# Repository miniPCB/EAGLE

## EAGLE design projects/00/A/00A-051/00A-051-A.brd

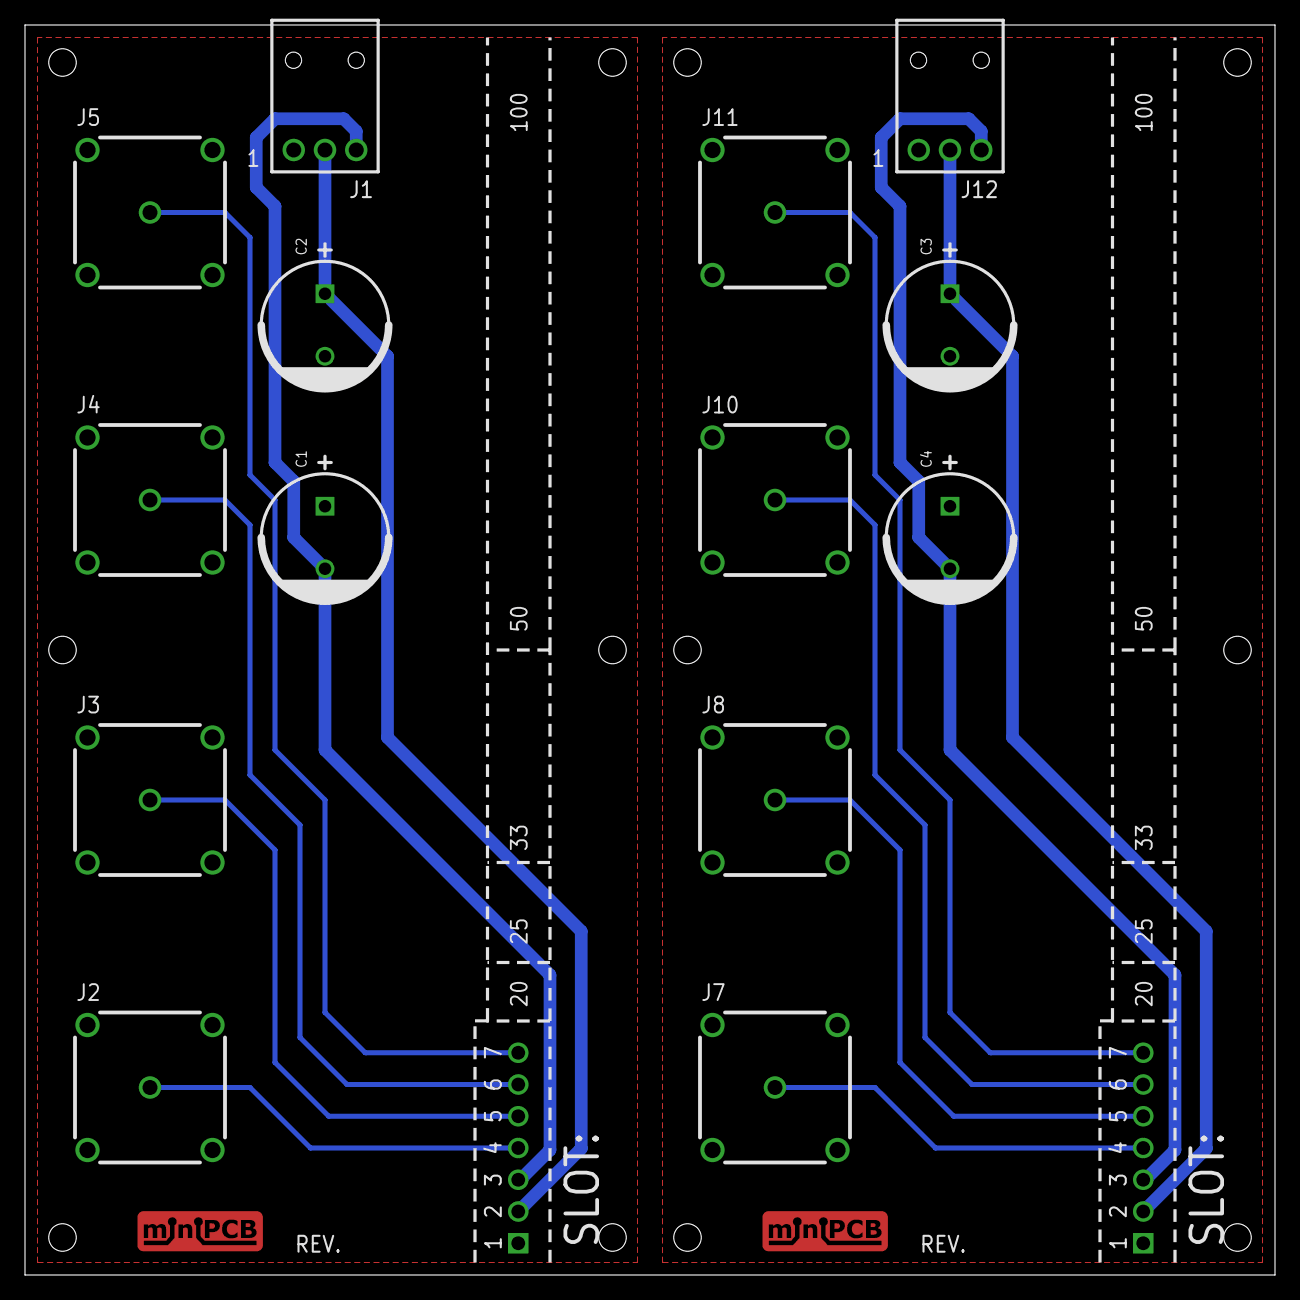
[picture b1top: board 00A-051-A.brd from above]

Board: 2 copper layers, 100.0 x 100.0 mm, 18 parts (0 on the bottom side), 14 nets.

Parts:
C1, C2, C3, C4: C5MM
J1, J12: NANOFIT-105313-1103; PINS_3-NANOFIT-H
J2, J7: J5.4; B35N14H
J3, J4, J5, J8, J10, J11: J5.5; B35N14H
J6, J9: A; MINIPCB_DOCK_7P
PCB, PCB1: MINIPCB_DOCK_50X100

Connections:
CH1: J2.1.SIG, J6.4
CH2: J3.1.SIG, J6.5
CH3: J4.1.SIG, J6.6
CH4: J5.1.SIG, J6.7
CH5: J7.1.SIG, J9.4
CH6: J8.1.SIG, J9.5
CH7: J9.6, J10.1.SIG
CH8: J9.7, J11.1.SIG
GND: C1.+, C2.-, J1.1, J2.2.GND, J2.3.GND, J2.4.GND, J2.5.GND, J3.2.GND, J3.3.GND, J3.4.GND, J3.5.GND, J4.2.GND, J4.3.GND, J4.4.GND, J4.5.GND, J5.2.GND, J5.3.GND, J5.4.GND, J5.5.GND, J6.1
GND1: C3.-, C4.+, J7.2.GND, J7.3.GND, J7.4.GND, J7.5.GND, J8.2.GND, J8.3.GND, J8.4.GND, J8.5.GND, J9.1, J10.2.GND, J10.3.GND, J10.4.GND, J10.5.GND, J11.2.GND, J11.3.GND, J11.4.GND, J11.5.GND, J12.1
V+: C2.+, J1.2, J6.2
V+1: C3.+, J9.2, J12.2
V-: C1.-, J1.3, J6.3
V-1: C4.-, J9.3, J12.3

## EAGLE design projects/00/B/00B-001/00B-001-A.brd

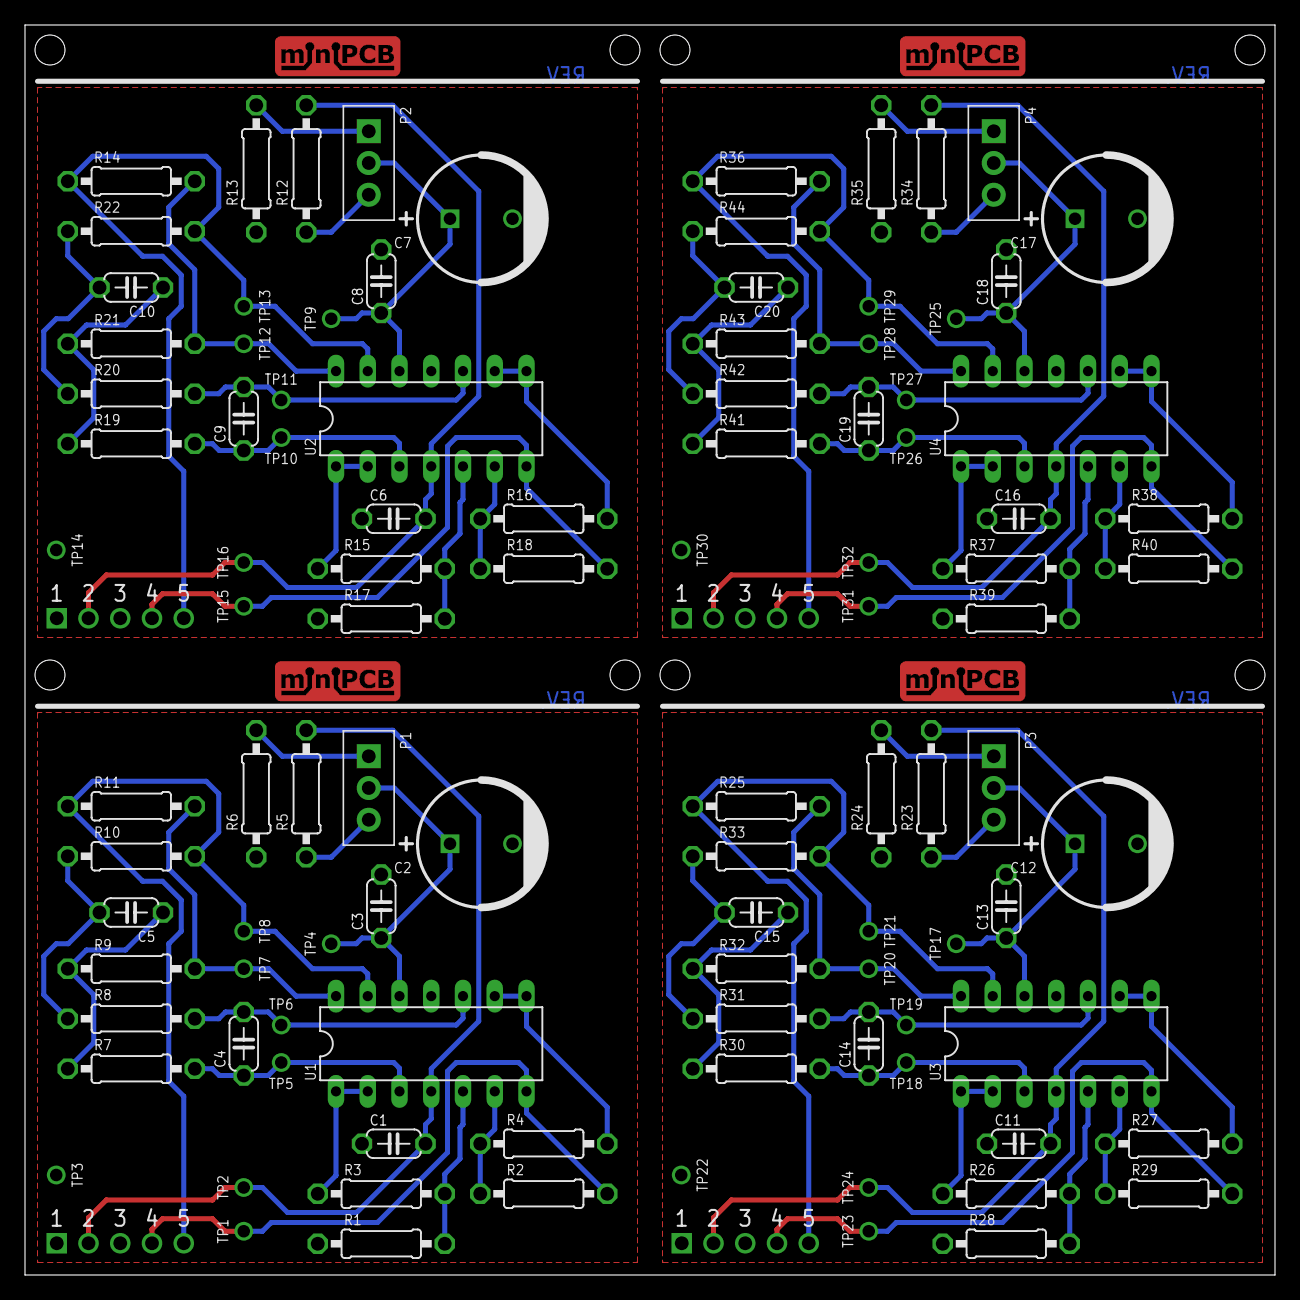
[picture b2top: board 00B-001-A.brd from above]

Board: 2 copper layers, 100.0 x 100.0 mm, 108 parts (0 on the bottom side), 64 nets.

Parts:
C1, C6, C11, C16: 1u; C050-024X044
C2, C7, C12, C17: C5MM
C3, C4, C5, C8, C9, C10, C13, C14, C15, C18, C19, C20: C050-024X044
J7-, J7-1, J7-2, J7-3: MINIPCB_5P_50X50MM
P1, P2, P3, P4: TRIM_0100
R1, R2, R3, R4, R5, R6, R7, R8, R9, R10, R11, R12, R13, R14, R15, R16, R17, R18, R19, R20, R21, R22, R23, R24, R25, R26, R27, R28, R29, R30, R31, R32, R33, R34, R35, R36, R37, R38, R39, R40, R41, R42, R43, R44: 0207/10
TP1, TP2, TP3, TP4, TP5, TP6, TP7, TP8, TP9, TP10, TP11, TP12, TP13, TP14, TP15, TP16, TP17, TP18, TP19, TP20, TP21, TP22, TP23, TP24, TP25, TP26, TP27, TP28, TP29, TP30, TP31, TP32: PINS_1_TESTPOINT_KE5000_NOTEXT
U1, U2, U3, U4: 324; DIL14

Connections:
GND: C1.2, C2.-, C3.2, J7-.1, R1.2, R6.1, TP3.1, U1.11
GND1: C6.2, C7.-, C8.2, J7-1.1, R13.1, R17.2, TP14.1, U2.11
GND2: C11.2, C12.-, C13.2, J7-2.1, R24.1, R28.2, TP22.1, U3.11
GND3: C16.2, C17.-, C18.2, J7-3.1, R35.1, R39.2, TP30.1, U4.11
unnamed: R9.1, R11.1, TP7.1, U1.14
unnamed: R3.1, U1.1, U1.2
unnamed: R4.1, U1.8, U1.9
unnamed: C2.+, C3.1, P1.2, TP4.1, U1.12
unnamed: P1.1, R6.2
unnamed: P1.3, R5.1
unnamed: J7-.5, R10.1, R11.2, TP8.1, U1.13
unnamed: R2.1, R4.2, U1.6
unnamed: R1.1, R3.2, U1.5
unnamed: J7-.4, R2.2, TP1.1, U1.7
unnamed: R14.1, R21.1, TP12.1, U2.14
unnamed: C7.+, C8.1, P2.2, TP9.1, U2.12
unnamed: P2.1, R13.2
unnamed: C4.1, R7.2, TP5.1, U1.3
unnamed: C4.2, R8.2, TP6.1, U1.10
unnamed: C5.1, R7.1, R9.2
unnamed: C5.2, R8.1, R10.2
unnamed: P2.3, R12.1
unnamed: J7-1.5, R14.2, R22.1, TP13.1, U2.13
unnamed: R15.1, U2.1, U2.2
unnamed: R16.1, U2.8, U2.9
unnamed: R16.2, R18.1, U2.6
unnamed: R15.2, R17.1, U2.5
unnamed: J7-1.4, R18.2, TP15.1, U2.7
unnamed: C9.1, R19.2, TP10.1, U2.3
unnamed: C9.2, R20.2, TP11.1, U2.10
unnamed: C10.1, R19.1, R21.2
unnamed: C10.2, R20.1, R22.2
unnamed: R25.1, R32.1, TP20.1, U3.14
unnamed: C12.+, C13.1, P3.2, TP17.1, U3.12
unnamed: P3.1, R24.2
unnamed: P3.3, R23.1
unnamed: J7-2.5, R25.2, R33.1, TP21.1, U3.13
unnamed: R26.1, U3.1, U3.2
unnamed: R27.1, U3.8, U3.9
unnamed: R27.2, R29.1, U3.6
unnamed: R26.2, R28.1, U3.5
unnamed: J7-2.4, R29.2, TP23.1, U3.7
unnamed: C14.1, R30.2, TP18.1, U3.3
unnamed: C14.2, R31.2, TP19.1, U3.10
unnamed: C15.1, R30.1, R32.2
unnamed: C15.2, R31.1, R33.2
unnamed: R36.1, R43.1, TP28.1, U4.14
unnamed: C17.+, C18.1, P4.2, TP25.1, U4.12
unnamed: P4.1, R35.2
unnamed: P4.3, R34.1
unnamed: J7-3.5, R36.2, R44.1, TP29.1, U4.13
unnamed: R37.1, U4.1, U4.2
unnamed: R38.1, U4.8, U4.9
unnamed: R38.2, R40.1, U4.6
unnamed: R37.2, R39.1, U4.5
unnamed: J7-3.4, R40.2, TP31.1, U4.7
unnamed: C19.1, R41.2, TP26.1, U4.3
unnamed: C19.2, R42.2, TP27.1, U4.10
unnamed: C20.1, R41.1, R43.2
unnamed: C20.2, R42.1, R44.2
V+: C1.1, J7-.2, R5.2, TP2.1, U1.4
V+1: C6.1, J7-1.2, R12.2, TP16.1, U2.4
V+2: C11.1, J7-2.2, R23.2, TP24.1, U3.4
V+3: C16.1, J7-3.2, R34.2, TP32.1, U4.4

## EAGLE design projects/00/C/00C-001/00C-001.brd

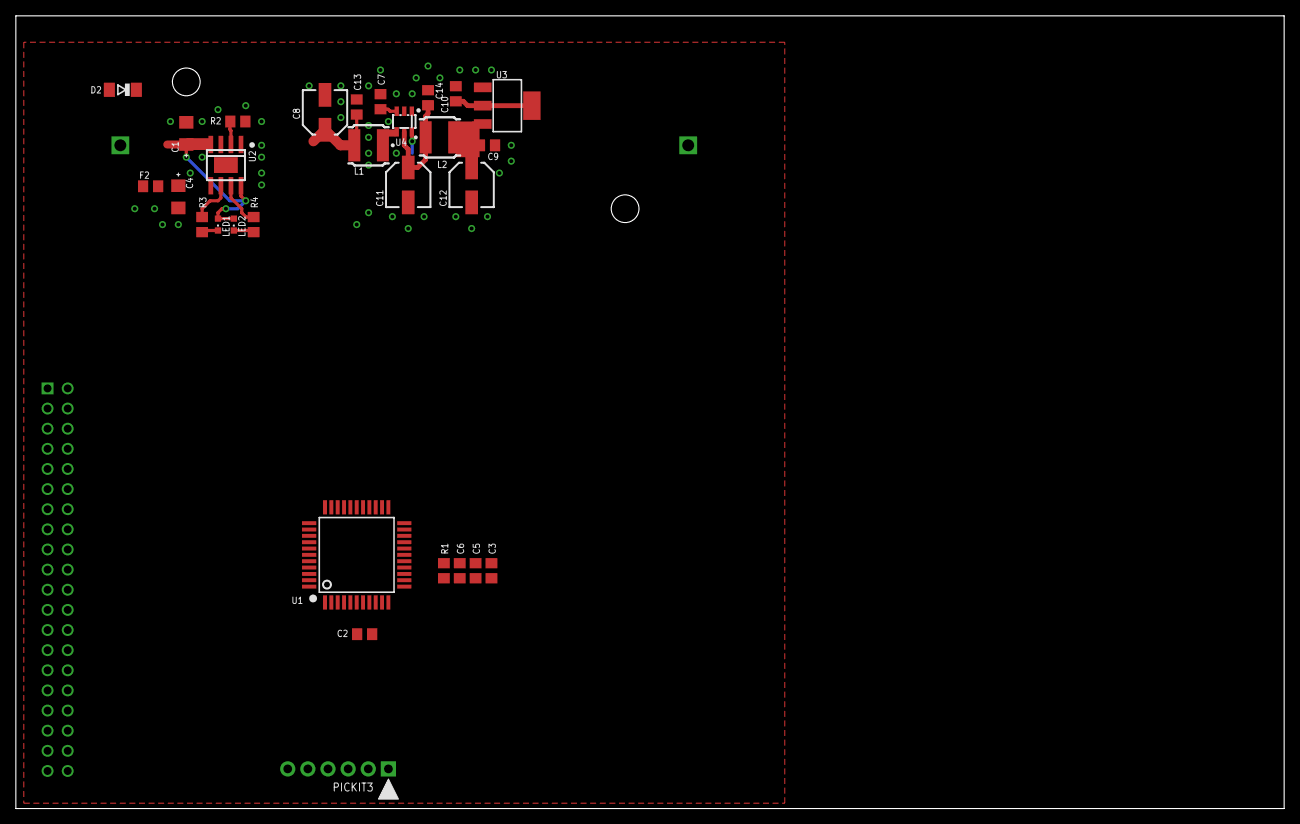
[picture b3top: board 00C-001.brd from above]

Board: 2 copper layers, 160.0 x 100.0 mm, 31 parts (1 on the bottom side), 20 nets.

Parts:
B1: 1043; BATTERY-18650-1
C1, C4: 10u, 1206; C1206
C2, C3, C5, C6: C0805
C7, C9, C10, C13, C14: 1u; C0805
C8, C11, C12: 47u; C-WE-5MM
D2: 1N5819; SOD80C
F2: 0805; F0805
J1-: RPI ZERO; RPI_ZERO
L1, L2: 22u; SRN5040
LED1: SBY; CHIPLED_0603
LED2: CHG; CHIPLED_0603
R1: R0805
R2: RPROG; R0805
R3, R4: 1k; R0805
U1: SQFP-S-10X10-44
U2: TP4056; SO08-THERMAL
U3: AMS1117-3.3; SOT223
U4: AP1603; SOT23-6
U$401: PICKIT3; PINS_6_PICKIT3

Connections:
+3V3: C10.2, U3.2, U3.4.TAB
+5V: C9.2, C12.1+, L2.1, U3.3
+BAT: C4.+, C8.1+, C13.2, F2.2, L1.1, U2.5
B+: B1.+, F2.1
CHARGE: R4.2, U2.7
DCDC_OUT: C11.1+, C14.2, L2.2, U4.5
DCDC_REF: C7.2, U4.3
GND: B1.1, C1.-, C2.2, C3.2, C4.-, C5.2, C6.2, C7.1, C8.2-, C9.1, C10.1, C11.2-, C12.2-, C13.1, C14.1, J1-.6, J1-.9, J1-.14, J1-.20, J1-.25, J1-.30, J1-.34, J1-.39, R2.1, U1.6, U1.29, U2.1, U2.3, U2.THERMAL, U3.1, U4.1, U4.2, U$401.3
unnamed: LED1.C, R3.1
unnamed: LED2.C, R4.1
unnamed: R2.2, U2.2
unnamed: U1.17, U$401.4
unnamed: U1.16, U$401.5
unnamed: R1.2, U1.18, U$401.1
PIC.RX: J1-.8, U1.1
PIC.TX: J1-.10, U1.44
PIC_VDD: C2.1, C3.1, C5.1, C6.1, R1.1, U1.7, U1.28, U$401.2
STANDBY: R3.2, U2.6
SWITCH_NODE: L1.2, U4.4
VCC: C1.+, D2.C, LED1.A, LED2.A, U2.4, U2.8

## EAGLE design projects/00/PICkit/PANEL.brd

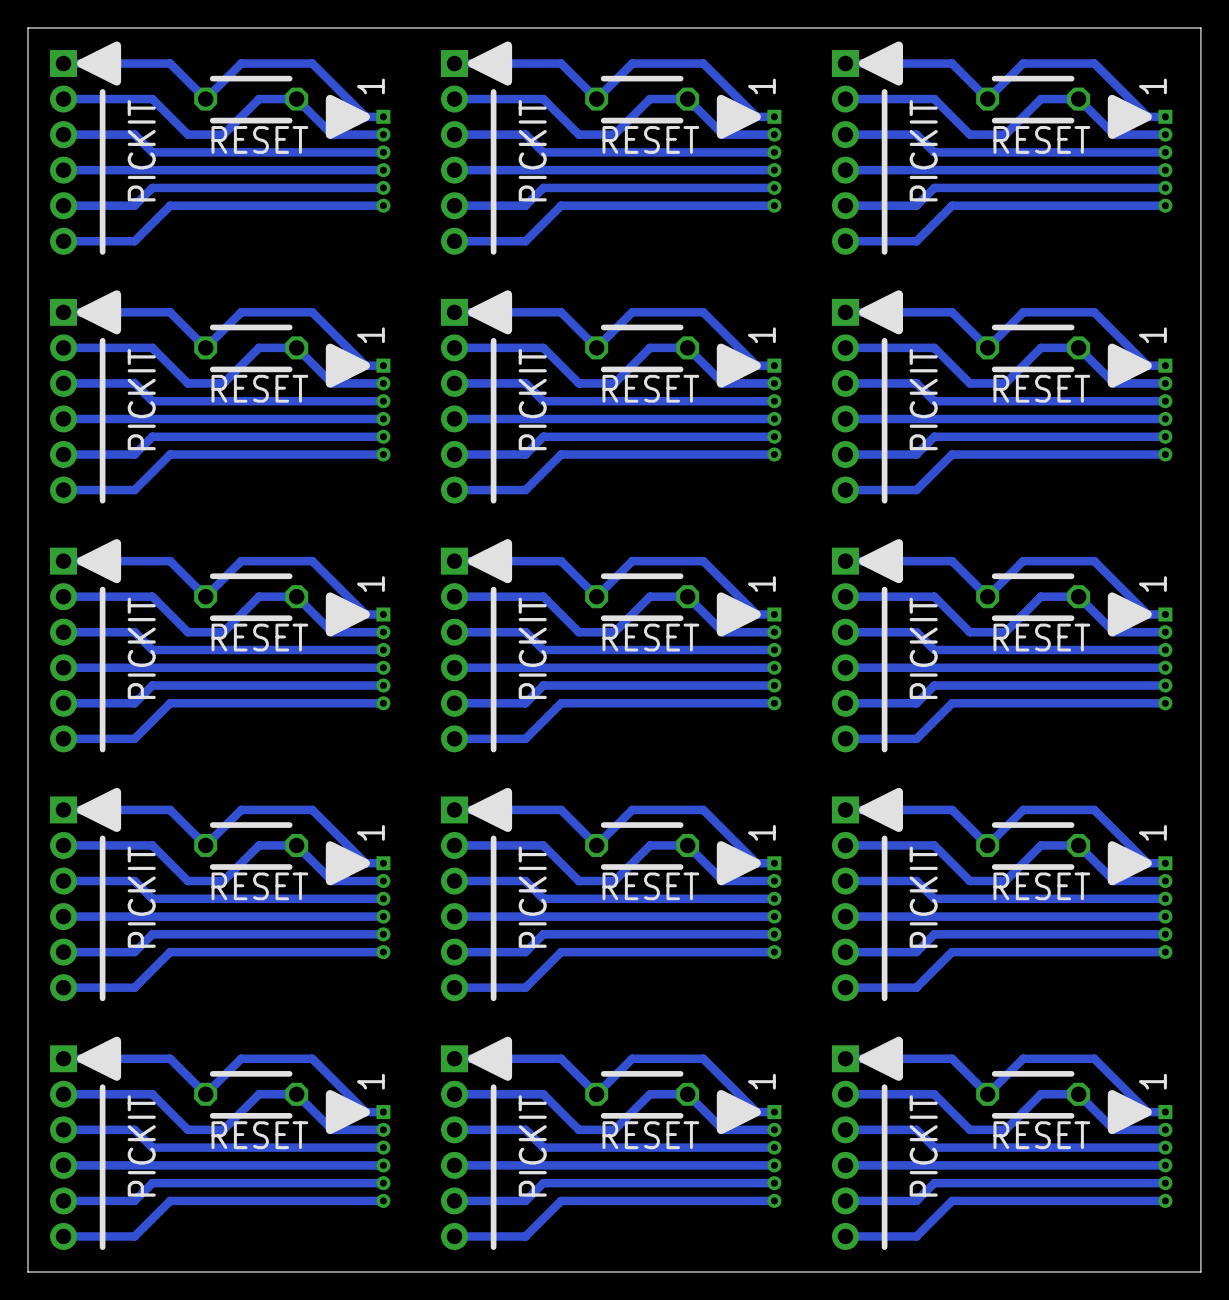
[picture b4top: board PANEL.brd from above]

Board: 2 copper layers, 83.8 x 88.9 mm, 45 parts (0 on the bottom side), 90 nets.

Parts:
RESET, RESET1, RESET2, RESET3, RESET4, RESET5, RESET6, RESET7, RESET8, RESET9, RESET10, RESET11, RESET12, RESET13, RESET14: 3X6MM
U$1, U$2, U$5, U$7, U$9, U$11, U$13, U$15, U$17, U$19, U$21, U$23, U$25, U$27, U$29: PICKIT3/1.27; PINS_6_1MM27
U$3, U$4, U$6, U$8, U$10, U$12, U$14, U$16, U$18, U$20, U$22, U$24, U$26, U$28, U$30: PICKIT; PINS_6_PICKIT3_TEXT

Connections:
unnamed: RESET.1, U$2.1, U$3.1
unnamed: RESET.2, U$2.2, U$3.2
unnamed: U$2.3, U$3.3
unnamed: U$2.4, U$3.4
unnamed: U$2.5, U$3.5
unnamed: U$2.6, U$3.6
unnamed: RESET1.1, U$1.1, U$4.1
unnamed: RESET1.2, U$1.2, U$4.2
unnamed: U$1.3, U$4.3
unnamed: U$1.4, U$4.4
unnamed: U$1.5, U$4.5
unnamed: U$1.6, U$4.6
unnamed: RESET2.1, U$5.1, U$6.1
unnamed: RESET2.2, U$5.2, U$6.2
unnamed: U$5.3, U$6.3
unnamed: U$5.4, U$6.4
unnamed: U$5.5, U$6.5
unnamed: U$5.6, U$6.6
unnamed: RESET3.1, U$7.1, U$8.1
unnamed: RESET3.2, U$7.2, U$8.2
unnamed: U$7.3, U$8.3
unnamed: U$7.4, U$8.4
unnamed: U$7.5, U$8.5
unnamed: U$7.6, U$8.6
unnamed: RESET4.1, U$9.1, U$10.1
unnamed: RESET4.2, U$9.2, U$10.2
unnamed: U$9.3, U$10.3
unnamed: U$9.4, U$10.4
unnamed: U$9.5, U$10.5
unnamed: U$9.6, U$10.6
unnamed: RESET5.1, U$11.1, U$12.1
unnamed: RESET5.2, U$11.2, U$12.2
unnamed: U$11.3, U$12.3
unnamed: U$11.4, U$12.4
unnamed: U$11.5, U$12.5
unnamed: U$11.6, U$12.6
unnamed: RESET6.1, U$13.1, U$14.1
unnamed: RESET6.2, U$13.2, U$14.2
unnamed: U$13.3, U$14.3
unnamed: U$13.4, U$14.4
unnamed: U$13.5, U$14.5
unnamed: U$13.6, U$14.6
unnamed: RESET7.1, U$15.1, U$16.1
unnamed: RESET7.2, U$15.2, U$16.2
unnamed: U$15.3, U$16.3
unnamed: U$15.4, U$16.4
unnamed: U$15.5, U$16.5
unnamed: U$15.6, U$16.6
unnamed: RESET8.1, U$17.1, U$18.1
unnamed: RESET8.2, U$17.2, U$18.2
unnamed: U$17.3, U$18.3
unnamed: U$17.4, U$18.4
unnamed: U$17.5, U$18.5
unnamed: U$17.6, U$18.6
unnamed: RESET9.1, U$19.1, U$20.1
unnamed: RESET9.2, U$19.2, U$20.2
unnamed: U$19.3, U$20.3
unnamed: U$19.4, U$20.4
unnamed: U$19.5, U$20.5
unnamed: U$19.6, U$20.6
unnamed: RESET10.1, U$21.1, U$22.1
unnamed: RESET10.2, U$21.2, U$22.2
unnamed: U$21.3, U$22.3
unnamed: U$21.4, U$22.4
unnamed: U$21.5, U$22.5
unnamed: U$21.6, U$22.6
unnamed: RESET11.1, U$23.1, U$24.1
unnamed: RESET11.2, U$23.2, U$24.2
unnamed: U$23.3, U$24.3
unnamed: U$23.4, U$24.4
unnamed: U$23.5, U$24.5
unnamed: U$23.6, U$24.6
unnamed: RESET12.1, U$25.1, U$26.1
unnamed: RESET12.2, U$25.2, U$26.2
unnamed: U$25.3, U$26.3
unnamed: U$25.4, U$26.4
unnamed: U$25.5, U$26.5
unnamed: U$25.6, U$26.6
unnamed: RESET13.1, U$27.1, U$28.1
unnamed: RESET13.2, U$27.2, U$28.2
unnamed: U$27.3, U$28.3
unnamed: U$27.4, U$28.4
unnamed: U$27.5, U$28.5
unnamed: U$27.6, U$28.6
unnamed: RESET14.1, U$29.1, U$30.1
unnamed: RESET14.2, U$29.2, U$30.2
unnamed: U$29.3, U$30.3
unnamed: U$29.4, U$30.4
unnamed: U$29.5, U$30.5
unnamed: U$29.6, U$30.6

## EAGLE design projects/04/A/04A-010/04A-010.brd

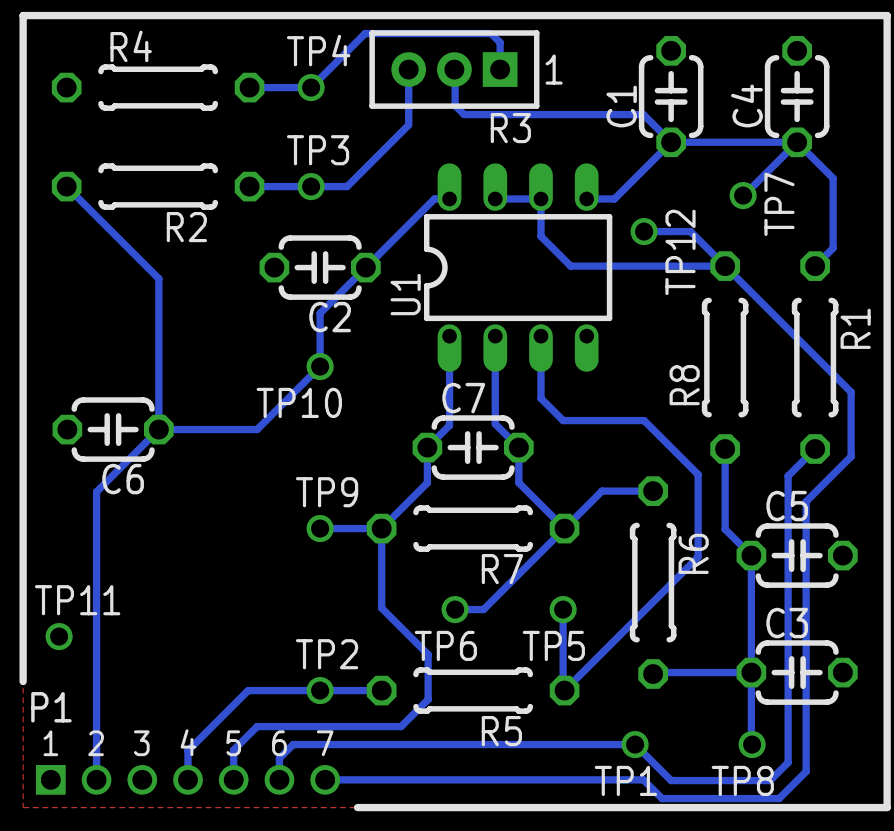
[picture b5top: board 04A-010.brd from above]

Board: 2 copper layers, 29 parts (0 on the bottom side), 12 nets.

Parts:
C1, C2, C3, C4, C5, C6, C7: C050-024X044
P1-: MINIPCB_7P_50X50
R1, R2, R4, R5, R6, R7, R8: 0207/10
R3: TRIM_0100
TP1, TP2, TP3, TP4, TP5, TP6, TP7, TP8, TP9, TP10, TP11, TP12: PINS_1_TESTPOINT_KE5000_NOTEXT
U1: DIL08

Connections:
BIAS: C1.1, C4.1, R1.1, R3.2, TP7.1, U1.5
BIAS_CONTROL: P1-.6, R1.2, TP1.1
GND: C1.2, C2.2, C3.2, C4.2, C5.2, C6.2, P1-.1, R4.1, TP11.1, U1.4
IN: P1-.4, R5.2, TP2.1
IN+: R5.1, TP5.1, U1.3
OUT: C7.1, P1-.5, R7.2, TP9.1, U1.1
POT.1: R3.1, R4.2, TP4.1
POT.3: R2.1, R3.3, TP3.1
V+: C2.1, C6.1, P1-.2, R2.2, TP10.1, U1.8
VFB: C7.2, R6.1, R7.1, TP6.1, U1.2
VREF: P1-.7, R8.2, TP12.1, U1.6, U1.7
VREF_FILTERED: C3.1, C5.1, R6.2, R8.1, TP8.1
